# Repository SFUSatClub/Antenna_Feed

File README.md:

#Antenna Feed printed circuit board
Board for feeding dipole antenna from unbalance radio board.

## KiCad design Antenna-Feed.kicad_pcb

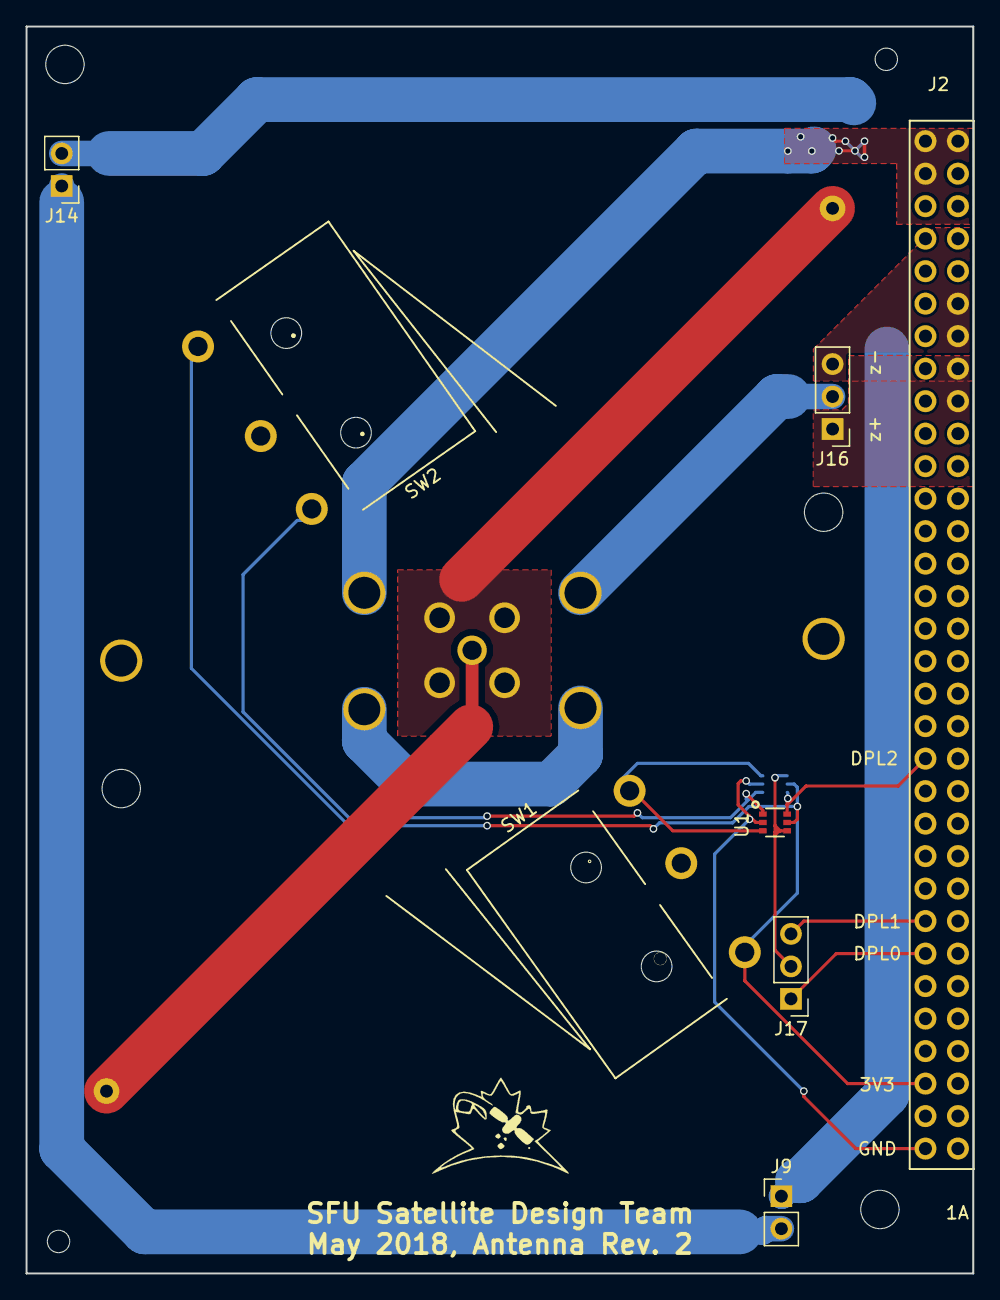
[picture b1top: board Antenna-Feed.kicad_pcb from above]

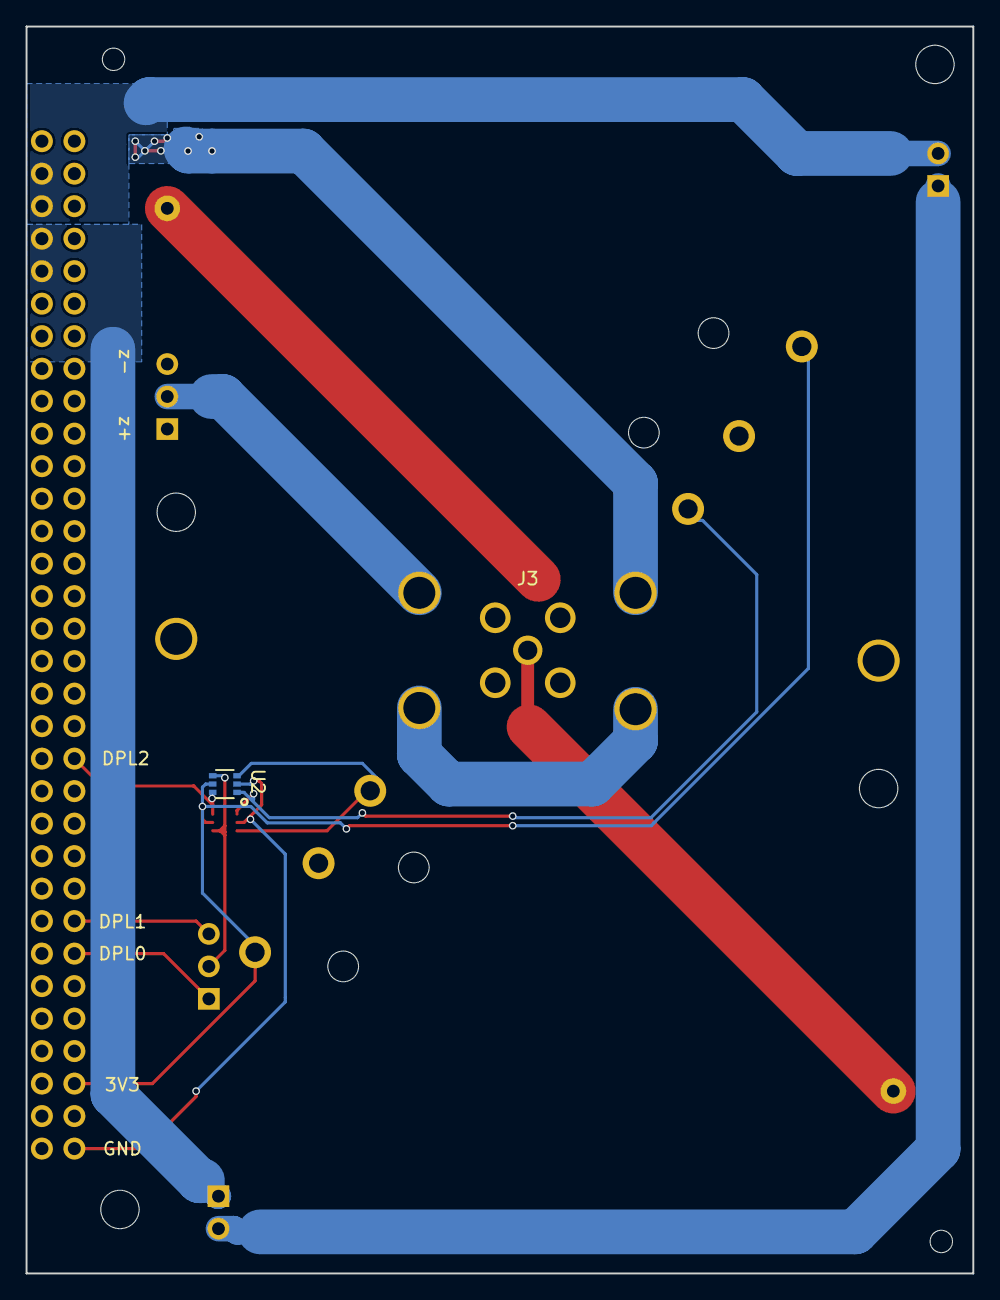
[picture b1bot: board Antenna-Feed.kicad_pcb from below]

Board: 2 copper layers, 74.0 x 97.5 mm, 18 parts (2 on the bottom side), 18 nets.

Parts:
J1, J4: Conn_01x01; via-0.97mm
J2: PC104-8BIT; PC104-8bit
J3: SMA; SMA-Vert-TH
J5, J6, J7, J8, J15, J18: Conn_01x01; PTH-2.5
J9, J14: Conn_01x02; Socket_Strip_Straight_1x02_Pitch2.54mm
J16, J17: Conn_01x03; Socket_Strip_Straight_1x03_Pitch2.54mm
SW1, SW2: LIMIT_SWITCH; SS-3GLPD-R
U1, U2: NC7SZ157; SOT-363

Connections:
/3V3: J2.3B, SW1.COM, SW2.COM, U1.5, U2.5
/DEPLOY.+Z: J2.24A, J2.25A, J16.1
/DEPLOY.-Z: J2.26A, J2.27A, J16.3
/GNDPWR: J2.31B, J2.32A, J2.32B, J5.1
/MUX/IN0: SW1.NC, U1.3, U2.3
/MUX/IN1: SW2.NC, U1.1, U2.1
/MUX/OUT: J17.2, U1.4, U2.4
/RF.DEPLOY0: J2.7B, J17.1
/RF.DEPLOY1: J2.8B, J17.3
/RF.DEPLOY2: J2.13B, U1.6, U2.6
/VSYS_DOWN: J2.28A, J2.29A, J9.1
/VSYS_UP: J2.30A, J2.31A, J14.2
GND: J2.1B, U1.2, U2.2
unnamed: J1.1, J3.1
unnamed: J3.2, J4.1
unnamed: J6.1, J8.1
unnamed: J9.2, J14.1
unnamed: J7.1, J16.2

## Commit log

2018-04-27 initial revision conforming to Ana's structural model
2018-04-29 Added through holes to the right side of the antenna feed pcb
2018-04-29 I forgot to save before the last push
2018-05-01 placed switches in accordance to latest structural model
2018-05-02 fine tuned component placement
2018-05-03 Fixed alignment of side connector pins. Added connector pins to left side.
2018-05-11 Pushing Work
2018-05-13 updated schematic
2018-05-13 connected nicrome posts in series
2018-05-13 Added new connectors to PCB and removed the old connectors from the left side.
2018-05-16 design complete
2018-05-16 generated gerbers
2018-05-16 added deployment connections
2018-06-04 board rev 2 complete
